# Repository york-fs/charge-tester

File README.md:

# BMS Charging Tester Board

A CAN-controlled linear charging board for testing BMS features without a full charger.

## Cloning

A recursive clone must be used to download the `kicad-library` repository:

    git clone --recursive https://github.com/york-fs/charge-tester.git

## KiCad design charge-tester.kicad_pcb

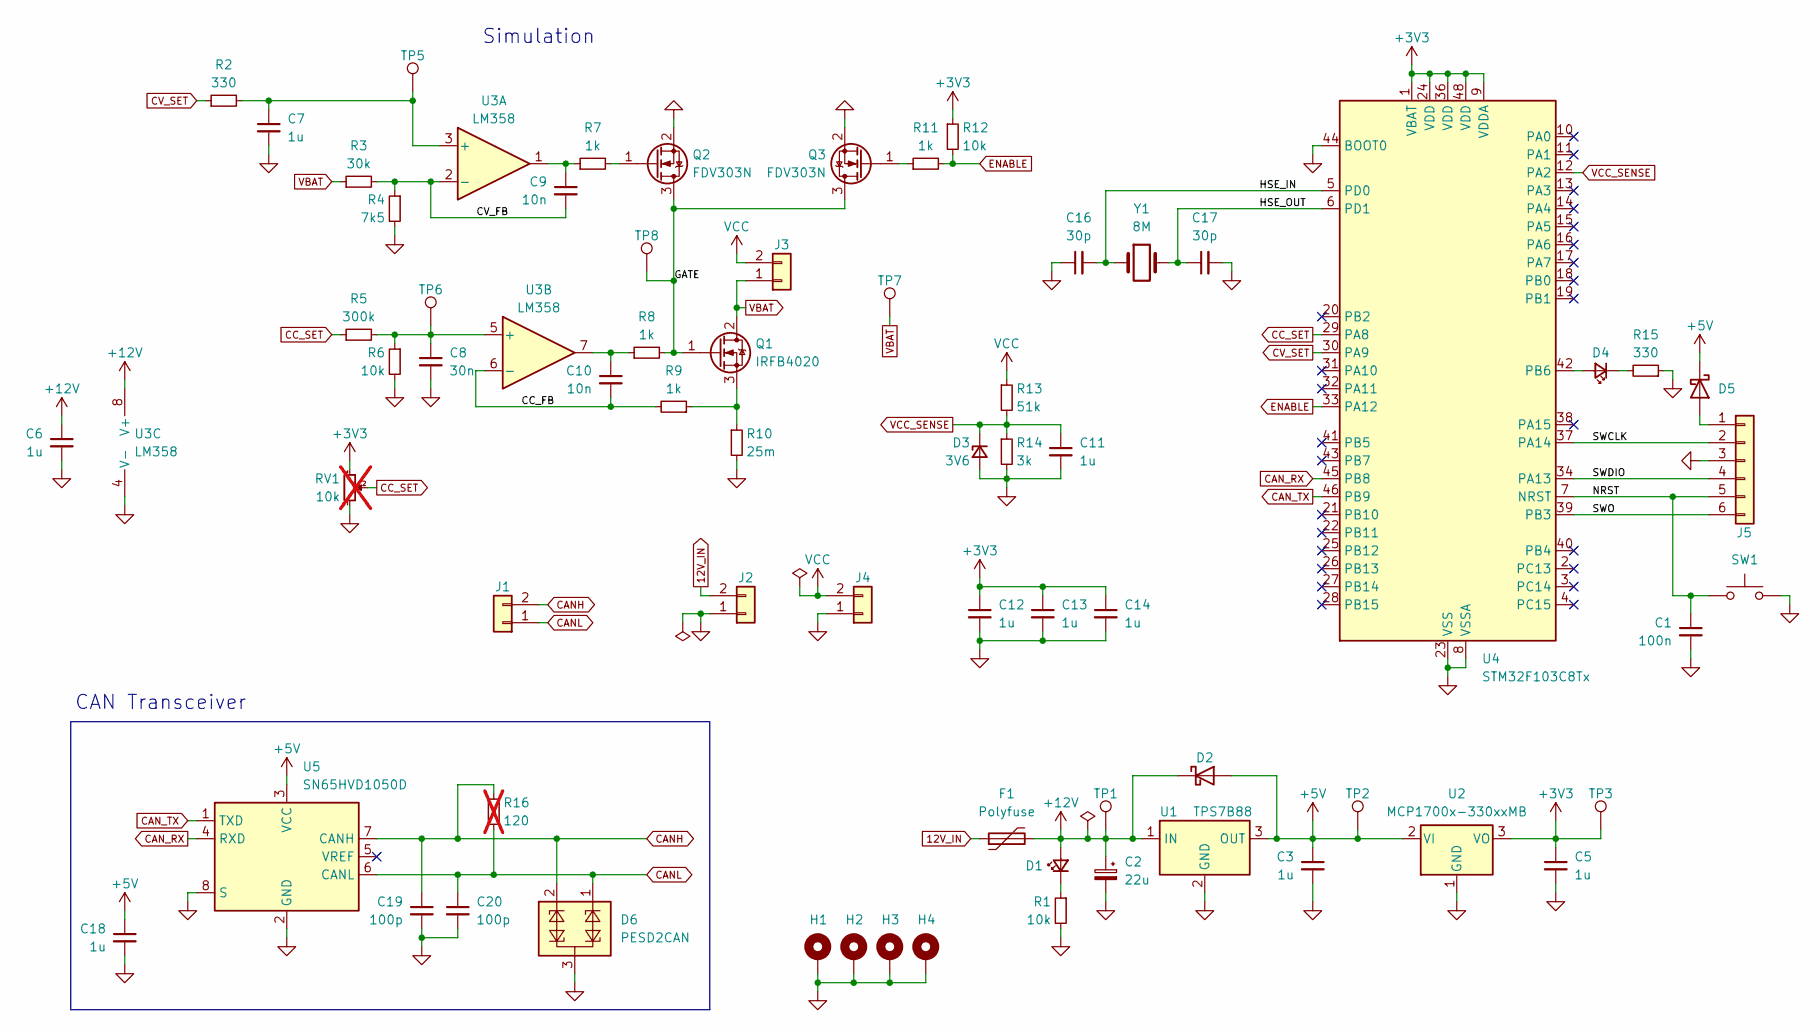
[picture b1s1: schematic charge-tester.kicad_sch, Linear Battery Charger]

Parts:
C1: 100n; C_0603_1608Metric; Mfr # CL10B104KB8NNNC
C2: 22u; CP_Elec_6.3x7.7; Mfr # EEEFK1J220XP
C3, C5, C6, C7, C11, C12, C13, C14, C18: 1u; C_0603_1608Metric; Mfr # CL10B105KB8NQNC
C8: 30n; C_0603_1608Metric
C9, C10: 10n; C_0603_1608Metric; Mfr # GRM1885C1H103JA01D
C16, C17: 30p; C_0603_1608Metric; Mfr # GQM1875C2E300GB12D
C19, C20: 100p; C_0603_1608Metric; Mfr # GCM1885C2A101JA16D
D1, D4: LED_Small; LED_0603_1608Metric; Mfr # NCD0603R1
D2, D5: D_Schottky; D_SOD-323; Mfr # NSR0530H
D3: 3V6; D_SOD-323; Mfr # BZX384C3V6
D6: PESD2CAN; SOT-23; Mfr # PESD2CAN,215
F1: Polyfuse; R_0805_2012Metric; Mfr # 0805L010/24YR
H1, H2, H3, H4: MountingHole_Pad; MountingHole_3.2mm_M3_Pad_Via
J1: Conn_01x02; MolexMicrofitPlus1x2; Mfr # 2157601012
J2: Conn_01x02; MolexMicrofitPlus1x2; Mfr # 2157601022
J3, J4: Conn_01x02; MolexMicrofitPlus1x2; Mfr # 2157601002
J5: Conn_01x06; IDC-Connector-2x3; Mfr # HX JN1.27-2x3P ZZ H4.9
Q1: IRFB4020; TO-220-3_Vertical
Q2, Q3: FDV303N; SOT-23; Mfr # FDV303N
R1, R6, R12: 10k; R_0603_1608Metric; Mfr # 0603WAF1002T5E
R2, R15: 330; R_0603_1608Metric; Mfr # 0603WAF3300T5E
R3: 30k; R_0603_1608Metric
R4: 7k5; R_0603_1608Metric
R5: 300k; R_0603_1608Metric
R7, R8, R9, R11: 1k; R_0603_1608Metric; Mfr # 0603WAF1001T5E
R10: 25m; R_1206_3216Metric; Mfr # HoJLR1206-1W-25mR-1%
R13: 51k; R_0603_1608Metric
R14: 3k; R_0603_1608Metric; Mfr # 0603WAF3001T5E
R16: 120; R_0603_1608Metric; not fitted
RV1: 10k; Potentiometer_Bourns_3296W_Vertical; not fitted
SW1: SW_Push; SW_Push_1P1T_NO_Vertical_Wuerth_434133025816; Mfr # SKRPACE010
TP1, TP2, TP3, TP5, TP6, TP7, TP8: TestPoint; TestPoint_Keystone_5000-5004_Miniature
U1: TPS7B88; TO-252-2; Mfr # TPS7B8850QKVURQ1
U2: MCP1700x-330xxMB; SOT-89-3; Mfr # MCP1700T-3302E/MB
U3: LM358; SOIC-8_3.9x4.9mm_P1.27mm; Mfr # LM358BAIDR
U4: STM32F103C8Tx; LQFP-48_7x7mm_P0.5mm; Mfr # STM32F103C8T6
U5: SN65HVD1050D; SOIC-8_3.9x4.9mm_P1.27mm; Mfr # SN65HVD1050DR
Y1: 8M; Crystal_SMD_5032-2Pin_5.0x3.2mm; Mfr # X50328MSB2GI

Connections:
12V_IN: F1.1, J2.2
+3V3: C5.1, C12.1, C13.1, C14.1, R12.1, RV1.1, TP3.1, U2.3 (VO), U4.1 (VBAT), U4.9 (VDDA), U4.24 (VDD), U4.36 (VDD), U4.48 (VDD)
+5V: C3.1, C18.1, D2.2 (A), D5.1 (K), TP2.1, U1.3 (OUT), U2.2 (VI), U5.3 (VCC)
+12V: C2.1, C6.1, D1.2 (A), D2.1 (K), F1.2, TP1.1, U1.1 (IN), U3.8 (V+)
/CC_FB: C10.2, R9.2, U3.6 (-)
/CV_FB: C9.2, R3.2, R4.1, U3.2 (-)
/GATE: Q1.1 (G), Q2.3 (D), Q3.3 (D), R8.2, TP8.1
/HSE_IN: C16.2, U4.5 (PD0), Y1.1
/HSE_OUT: C17.1, U4.6 (PD1), Y1.2
/NRST: C1.1, J5.5, SW1.1, U4.7 (NRST)
/SWCLK: J5.2, U4.37 (PA14)
/SWDIO: J5.4, U4.34 (PA13)
/SWO: J5.6, U4.39 (PB3)
CANH: C19.1, D6.2 (C2), J1.2, R16.1, U5.7 (CANH)
CANL: C20.1, D6.1 (C1), J1.1, R16.2, U5.6 (CANL)
CAN_RX: U4.45 (PB8), U5.4 (RXD)
CAN_TX: U4.46 (PB9), U5.1 (TXD)
CC_SET: R5.1, RV1.2, U4.29 (PA8)
CV_SET: R2.1, U4.30 (PA9)
ENABLE: R11.2, R12.2, U4.33 (PA12)
GND: C1.2, C2.2, C3.2, C5.2, C6.2, C7.2, C8.2, C11.2, C12.2, C13.2, C14.2, C16.1, C17.2, C18.2, C19.2, C20.2, D3.2 (A), D6.3 (CC), H1.1, H2.1, H3.1, H4.1, J2.1, J4.1, J5.3, Q2.2 (S), Q3.2 (S), R1.2, R4.2, R6.2, R10.2, R14.2, R15.1, RV1.3, SW1.2, U1.2 (GND), U2.1 (GND), U3.4 (V-), U4.8 (VSSA), U4.23 (VSS), U4.35 (VSS), U4.44 (BOOT0), U4.47 (VSS), U5.2 (GND), U5.8 (S)
unnamed: C9.1, R7.1, U3.1
unnamed: C10.1, R8.1, U3.7
unnamed: D1.1 (K), R1.1
unnamed: D4.2 (A), U4.42 (PB6)
unnamed: D4.1 (K), R15.2
unnamed: D5.2 (A), J5.1
unnamed: Q1.3 (S), R9.1, R10.1
unnamed: Q2.1 (G), R7.2
unnamed: Q3.1 (G), R11.1
unnamed: C7.1, R2.2, TP5.1, U3.3 (+)
unnamed: C8.1, R5.2, R6.1, TP6.1, U3.5 (+)
VBAT: J3.1, Q1.2 (D), R3.1, TP7.1
VCC: J3.2, J4.2, R13.1
VCC_SENSE: C11.1, D3.1 (K), R13.2, R14.1, U4.12 (PA2)

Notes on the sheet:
Simulation
CAN Transceiver

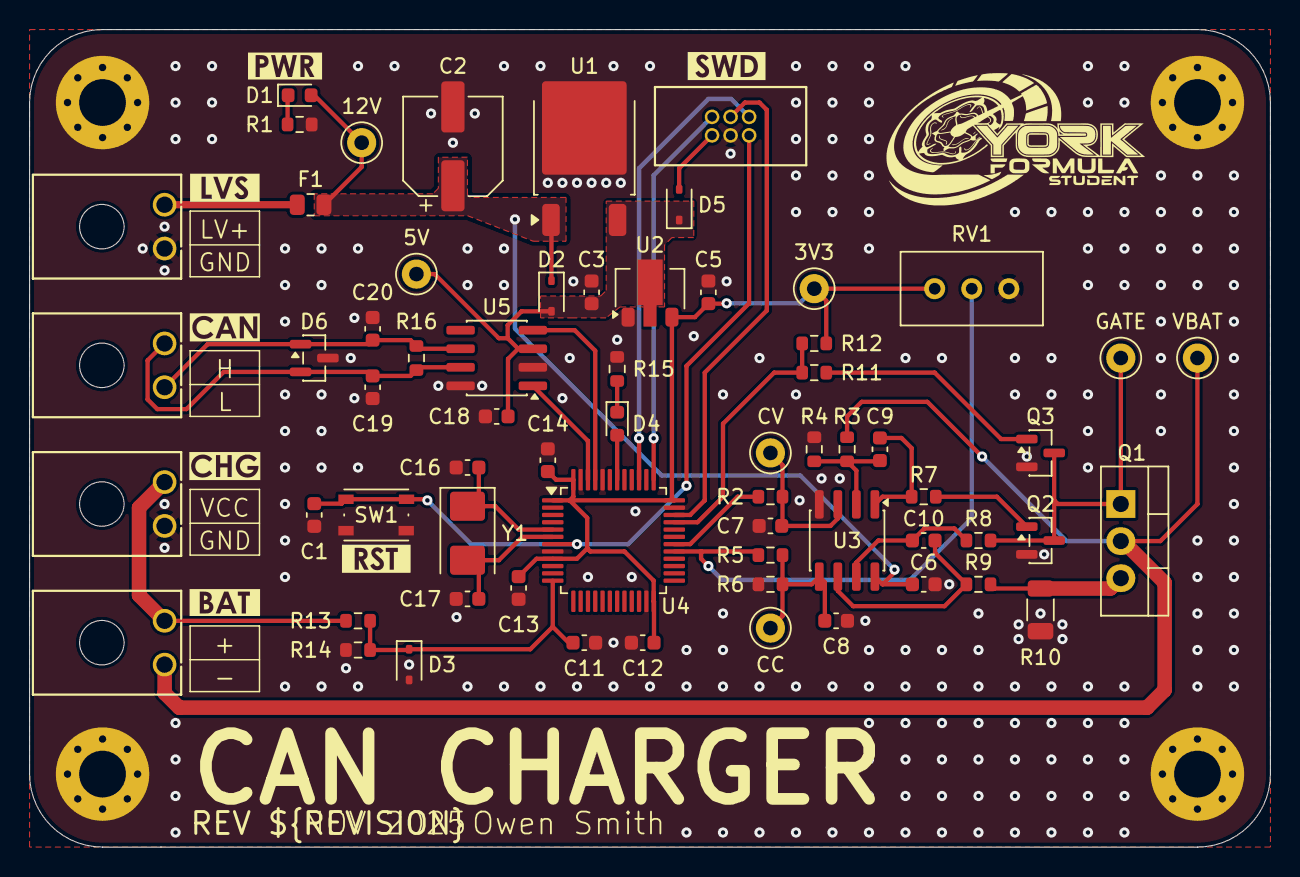
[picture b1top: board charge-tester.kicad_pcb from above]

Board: 2 copper layers, 85.0 x 56.0 mm, 75 parts (0 on the bottom side), 35 nets.

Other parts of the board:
kibuzzard-691F9AB4: G***; kibuzzard-691F9AB4
kibuzzard-691FA72C: G***; kibuzzard-691FA72C
kibuzzard-6910B7D7: G***; kibuzzard-6910B7D7
kibuzzard-6910B743: G***; kibuzzard-6910B743
kibuzzard-6910BB6B: G***; kibuzzard-6910BB6B
kibuzzard-6910BB45: G***; kibuzzard-6910BB45
kibuzzard-6910BB76: G***; kibuzzard-6910BB76

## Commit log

2025-11-20 schematic: Assign footprints and fill out BOM
2025-11-20 schematic: Add some more test points and net labels
2025-11-21 *: Initial layout
2025-11-21 pcb: Upgrade to 1 mm traces for the main current path
2025-11-21 pcb: Improve silkscreen
2025-11-22 *: Fill in info boxes
2025-11-22 pcb: Run cleanup tracks
2025-11-22 pcb: Set gerber output parameters
2025-11-22 meta: Update gitignore
2025-11-23 ci: Add kicad workflow
2025-11-23 meta: Create a README
2025-12-06 schematic: Switch op-amp to LM358BA
2026-01-11 bom: Fix incorrect 3k resistor part number
